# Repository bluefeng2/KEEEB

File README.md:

# KEEEB
Making a mechanical keyboard with LED lighting.
This keyboard has a 67 key layout, similar to a 60% keyboard.

I made this project, because I wanted a mechanical keyboard, and to learn how to design pcbs. I felt this would be a challenging project that would make me something I want to use daily.

.png)

## 3d Model:
Made in Fusion 360

.webp)

## PCB:
Made in KiCAD

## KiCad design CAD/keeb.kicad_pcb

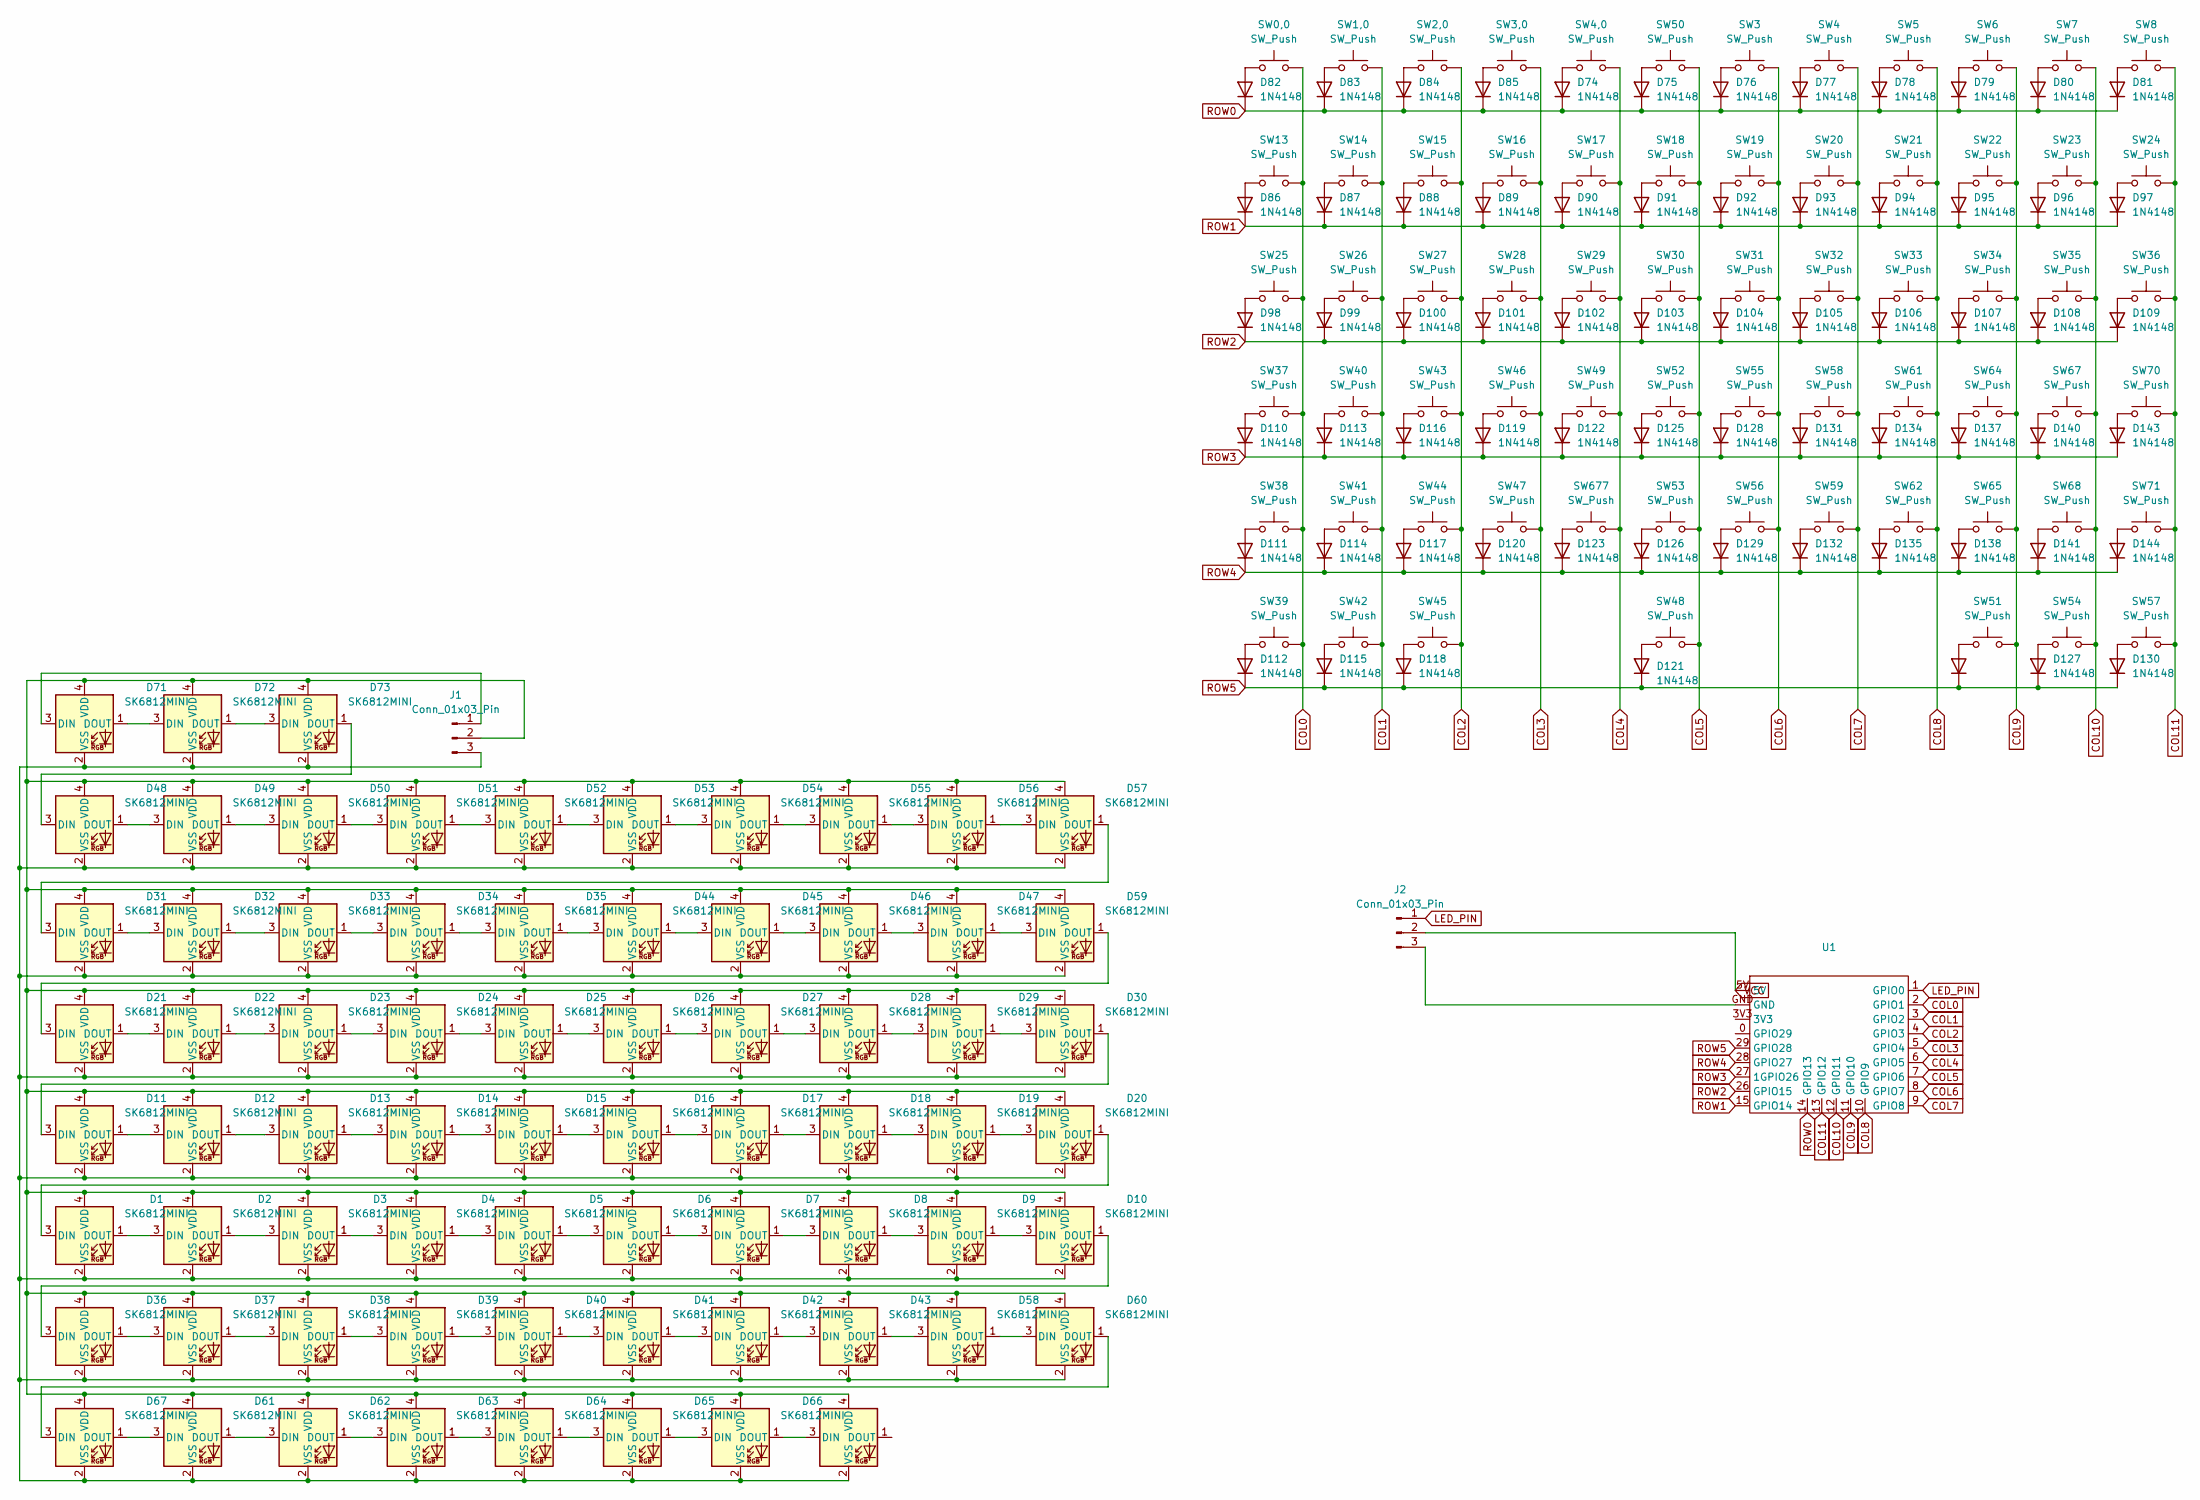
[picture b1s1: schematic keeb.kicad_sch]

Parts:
D1, D2, D3, D4, D5, D6, D7, D8, D9, D10, D11, D12, D13, D14, D15, D16, D17, D18, D19, D20, D21, D22, D23, D24, D25, D26, D27, D28, D29, D30, D31, D32, D33, D34, D35, D36, D37, D38, D39, D40, D41, D42, D43, D44, D45, D46, D47, D48, D49, D50, D51, D52, D53, D54, D55, D56, D57, D58, D59, D60, D61, D62, D63, D64, D65, D66, D67, D68, D71, D72, D73: SK6812MINI; LED_SK6812MINI_PLCC4_3.5x3.5mm_P1.75mm
D74, D75, D76, D77, D78, D79, D80, D81, D82, D83, D84, D85, D86, D87, D88, D89, D90, D91, D92, D93, D94, D95, D96, D97, D98, D99, D100, D101, D102, D103, D104, D105, D106, D107, D108, D109, D110, D111, D112, D113, D114, D115, D116, D117, D118, D119, D120, D121, D122, D123, D124, D125, D126, D127, D128, D129, D130, D131, D132, D134, D135, D137, D138, D140, D141, D143, D144: 1N4148; D_DO-35_SOD27_P7.62mm_Horizontal
J1, J2: Conn_01x03_Pin; PinHeader_1x03_P1.00mm_Vertical
SW0,0, SW1,0, SW2,0, SW3, SW3,0, SW4, SW4,0, SW5, SW6, SW8, SW14, SW17, SW18, SW20, SW21, SW22, SW23, SW24, SW27, SW28, SW29, SW30: SW_Push; SW_Cherry_MX_1.00u_Plate
SW7, SW15, SW16, SW19, SW26, SW31, SW32, SW33, SW34, SW35, SW36, SW38, SW40, SW41, SW43, SW44, SW46, SW47, SW49, SW50, SW52, SW55, SW57, SW58, SW59, SW61, SW64, SW65, SW67, SW68, SW71, SW677: SW_Push; SW_Cherry_MX_1.00u_PCB
SW13, SW39, SW53, SW54: SW_Push; SW_Cherry_MX_1.50u_PCB
SW25, SW70: SW_Push; SW_Cherry_MX_1.75u_PCB
SW37, SW62: SW_Push; SW_Cherry_MX_2.25u_PCB
SW42, SW45, SW51: SW_Push; SW_Cherry_MX_1.25u_PCB
SW48: SW_Push; SW_Cherry_MX_6.25u_PCB
SW56: SW_Push; SW_Cherry_MX_2.00u_PCB
U1: RP2040-Tiny

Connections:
COL0: SW0,0.2, SW13.2, SW25.2, SW37.2, SW38.2, SW39.2, U1.2 (GPIO1)
COL1: SW1,0.2, SW14.2, SW26.2, SW40.2, SW41.2, SW42.2, U1.3 (GPIO2)
COL2: SW2,0.2, SW15.2, SW27.2, SW43.2, SW44.2, SW45.2, U1.4 (GPIO3)
COL3: SW3,0.2, SW16.2, SW28.2, SW46.2, SW47.2, U1.5 (GPIO4)
COL4: SW4,0.2, SW17.2, SW29.2, SW49.2, SW677.2, U1.6 (GPIO5)
COL5: SW18.2, SW30.2, SW48.2, SW50.2, SW52.2, SW53.2, U1.7 (GPIO6)
COL6: SW3.2, SW19.2, SW31.2, SW55.2, SW56.2, U1.8 (GPIO7)
COL7: SW4.2, SW20.2, SW32.2, SW58.2, SW59.2, U1.9 (GPIO8)
COL8: SW5.2, SW21.2, SW33.2, SW61.2, SW62.2, U1.10 (GPIO9)
COL9: SW6.2, SW22.2, SW34.2, SW51.2, SW64.2, SW65.2, U1.11 (GPIO10)
COL10: SW7.2, SW23.2, SW35.2, SW54.2, SW67.2, SW68.2, U1.12 (GPIO11)
COL11: SW8.2, SW24.2, SW36.2, SW57.2, SW70.2, SW71.2, U1.13 (GPIO12)
LED_PIN: J2.1, U1.1 (GPIO0)
unnamed: D1.3 (DIN), D20.1 (DOUT)
unnamed: D1.1 (DOUT), D2.3 (DIN)
unnamed: D1.4 (VDD), D2.4 (VDD), D3.4 (VDD), D4.4 (VDD), D5.4 (VDD), D6.4 (VDD), D7.4 (VDD), D8.4 (VDD), D9.4 (VDD), D10.4 (VDD), D11.4 (VDD), D12.4 (VDD), D13.4 (VDD), D14.4 (VDD), D15.4 (VDD), D16.4 (VDD), D17.4 (VDD), D18.4 (VDD), D19.4 (VDD), D20.4 (VDD), D21.4 (VDD), D22.4 (VDD), D23.4 (VDD), D24.4 (VDD), D25.4 (VDD), D26.4 (VDD), D27.4 (VDD), D28.4 (VDD), D29.4 (VDD), D30.4 (VDD), D31.4 (VDD), D32.4 (VDD), D33.4 (VDD), D34.4 (VDD), D35.4 (VDD), D36.4 (VDD), D37.4 (VDD), D38.4 (VDD), D39.4 (VDD), D40.4 (VDD), D41.4 (VDD), D42.4 (VDD), D43.4 (VDD), D44.4 (VDD), D45.4 (VDD), D46.4 (VDD), D47.4 (VDD), D48.4 (VDD), D49.4 (VDD), D50.4 (VDD), D51.4 (VDD), D52.4 (VDD), D53.4 (VDD), D54.4 (VDD), D55.4 (VDD), D56.4 (VDD), D57.4 (VDD), D58.4 (VDD), D59.4 (VDD), D60.4 (VDD), D61.4 (VDD), D62.4 (VDD), D63.4 (VDD), D64.4 (VDD), D65.4 (VDD), D66.4 (VDD), D67.4 (VDD), D68.4 (VDD), D71.4 (VDD), D72.4 (VDD), D73.4 (VDD), J1.2
unnamed: D1.2 (VSS), D2.2 (VSS), D3.2 (VSS), D4.2 (VSS), D5.2 (VSS), D6.2 (VSS), D7.2 (VSS), D8.2 (VSS), D9.2 (VSS), D10.2 (VSS), D11.2 (VSS), D12.2 (VSS), D13.2 (VSS), D14.2 (VSS), D15.2 (VSS), D16.2 (VSS), D17.2 (VSS), D18.2 (VSS), D19.2 (VSS), D20.2 (VSS), D21.2 (VSS), D22.2 (VSS), D23.2 (VSS), D24.2 (VSS), D25.2 (VSS), D26.2 (VSS), D27.2 (VSS), D28.2 (VSS), D29.2 (VSS), D30.2 (VSS), D31.2 (VSS), D32.2 (VSS), D33.2 (VSS), D34.2 (VSS), D35.2 (VSS), D36.2 (VSS), D37.2 (VSS), D38.2 (VSS), D39.2 (VSS), D40.2 (VSS), D41.2 (VSS), D42.2 (VSS), D43.2 (VSS), D44.2 (VSS), D45.2 (VSS), D46.2 (VSS), D47.2 (VSS), D48.2 (VSS), D49.2 (VSS), D50.2 (VSS), D51.2 (VSS), D52.2 (VSS), D53.2 (VSS), D54.2 (VSS), D55.2 (VSS), D56.2 (VSS), D57.2 (VSS), D58.2 (VSS), D59.2 (VSS), D60.2 (VSS), D61.2 (VSS), D62.2 (VSS), D63.2 (VSS), D64.2 (VSS), D65.2 (VSS), D66.2 (VSS), D67.2 (VSS), D68.2 (VSS), D71.2 (VSS), D72.2 (VSS), D73.2 (VSS), J1.3
unnamed: D2.1 (DOUT), D3.3 (DIN)
unnamed: D3.1 (DOUT), D4.3 (DIN)
unnamed: D4.1 (DOUT), D5.3 (DIN)
unnamed: D5.1 (DOUT), D6.3 (DIN)
unnamed: D6.1 (DOUT), D7.3 (DIN)
unnamed: D7.1 (DOUT), D8.3 (DIN)
unnamed: D8.1 (DOUT), D9.3 (DIN)
unnamed: D9.1 (DOUT), D10.3 (DIN)
unnamed: D10.1 (DOUT), D36.3 (DIN)
unnamed: D11.3 (DIN), D30.1 (DOUT)
unnamed: D11.1 (DOUT), D12.3 (DIN)
unnamed: D12.1 (DOUT), D13.3 (DIN)
unnamed: D13.1 (DOUT), D14.3 (DIN)
unnamed: D14.1 (DOUT), D15.3 (DIN)
unnamed: D15.1 (DOUT), D16.3 (DIN)
unnamed: D16.1 (DOUT), D17.3 (DIN)
unnamed: D17.1 (DOUT), D18.3 (DIN)
unnamed: D18.1 (DOUT), D19.3 (DIN)
unnamed: D19.1 (DOUT), D20.3 (DIN)
unnamed: D21.3 (DIN), D59.1 (DOUT)
unnamed: D21.1 (DOUT), D22.3 (DIN)
unnamed: D22.1 (DOUT), D23.3 (DIN)
unnamed: D23.1 (DOUT), D24.3 (DIN)
unnamed: D24.1 (DOUT), D25.3 (DIN)
unnamed: D25.1 (DOUT), D26.3 (DIN)
unnamed: D26.1 (DOUT), D27.3 (DIN)
unnamed: D27.1 (DOUT), D28.3 (DIN)
unnamed: D28.1 (DOUT), D29.3 (DIN)
unnamed: D29.1 (DOUT), D30.3 (DIN)
unnamed: D31.3 (DIN), D57.1 (DOUT)
unnamed: D31.1 (DOUT), D32.3 (DIN)
unnamed: D32.1 (DOUT), D33.3 (DIN)
unnamed: D33.1 (DOUT), D34.3 (DIN)
unnamed: D34.1 (DOUT), D35.3 (DIN)
unnamed: D35.1 (DOUT), D44.3 (DIN)
unnamed: D36.1 (DOUT), D37.3 (DIN)
unnamed: D37.1 (DOUT), D38.3 (DIN)
unnamed: D38.1 (DOUT), D39.3 (DIN)
unnamed: D39.1 (DOUT), D40.3 (DIN)
unnamed: D40.1 (DOUT), D41.3 (DIN)
unnamed: D41.1 (DOUT), D42.3 (DIN)
unnamed: D42.1 (DOUT), D43.3 (DIN)
unnamed: D43.1 (DOUT), D58.3 (DIN)
unnamed: D44.1 (DOUT), D45.3 (DIN)
unnamed: D45.1 (DOUT), D46.3 (DIN)
unnamed: D46.1 (DOUT), D47.3 (DIN)
unnamed: D47.1 (DOUT), D59.3 (DIN)
unnamed: D48.3 (DIN), D73.1 (DOUT)
unnamed: D48.1 (DOUT), D49.3 (DIN)
unnamed: D49.1 (DOUT), D50.3 (DIN)
unnamed: D50.1 (DOUT), D51.3 (DIN)
unnamed: D51.1 (DOUT), D52.3 (DIN)
unnamed: D52.1 (DOUT), D53.3 (DIN)
unnamed: D53.1 (DOUT), D54.3 (DIN)
unnamed: D54.1 (DOUT), D55.3 (DIN)
unnamed: D55.1 (DOUT), D56.3 (DIN)
unnamed: D56.1 (DOUT), D57.3 (DIN)
unnamed: D58.1 (DOUT), D60.3 (DIN)
unnamed: D60.1 (DOUT), D67.3 (DIN)
unnamed: D61.3 (DIN), D67.1 (DOUT)
unnamed: D61.1 (DOUT), D62.3 (DIN)
unnamed: D62.1 (DOUT), D63.3 (DIN)
unnamed: D63.1 (DOUT), D64.3 (DIN)
unnamed: D64.1 (DOUT), D65.3 (DIN)
unnamed: D65.1 (DOUT), D66.3 (DIN)
unnamed: D66.1 (DOUT), D68.3 (DIN)
unnamed: D71.3 (DIN), J1.1
unnamed: D71.1 (DOUT), D72.3 (DIN)
unnamed: D72.1 (DOUT), D73.3 (DIN)
unnamed: D74.2 (A), SW4,0.1
unnamed: D75.2 (A), SW50.1
unnamed: D76.2 (A), SW3.1
unnamed: D77.2 (A), SW4.1
unnamed: D78.2 (A), SW5.1
unnamed: D79.2 (A), SW6.1
unnamed: D80.2 (A), SW7.1
unnamed: D81.2 (A), SW8.1
unnamed: D82.2 (A), SW0,0.1
unnamed: D83.2 (A), SW1,0.1
unnamed: D84.2 (A), SW2,0.1
unnamed: D85.2 (A), SW3,0.1
unnamed: D86.2 (A), SW13.1
unnamed: D87.2 (A), SW14.1
unnamed: D88.2 (A), SW15.1
unnamed: D89.2 (A), SW16.1
unnamed: D90.2 (A), SW17.1
unnamed: D91.2 (A), SW18.1
unnamed: D92.2 (A), SW19.1
unnamed: D93.2 (A), SW20.1
unnamed: D94.2 (A), SW21.1
unnamed: D95.2 (A), SW22.1
unnamed: D96.2 (A), SW23.1
unnamed: D97.2 (A), SW24.1
unnamed: D98.2 (A), SW25.1
unnamed: D99.2 (A), SW26.1
unnamed: D100.2 (A), SW27.1
unnamed: D101.2 (A), SW28.1
unnamed: D102.2 (A), SW29.1
unnamed: D103.2 (A), SW30.1
unnamed: D104.2 (A), SW31.1
unnamed: D105.2 (A), SW32.1
unnamed: D106.2 (A), SW33.1
unnamed: D107.2 (A), SW34.1
unnamed: D108.2 (A), SW35.1
unnamed: D109.2 (A), SW36.1
unnamed: D110.2 (A), SW37.1
unnamed: D111.2 (A), SW38.1
unnamed: D112.2 (A), SW39.1
unnamed: D113.2 (A), SW40.1
unnamed: D114.2 (A), SW41.1
unnamed: D115.2 (A), SW42.1
unnamed: D116.2 (A), SW43.1
unnamed: D117.2 (A), SW44.1
unnamed: D118.2 (A), SW45.1
unnamed: D119.2 (A), SW46.1
unnamed: D120.2 (A), SW47.1
unnamed: D121.2 (A), SW48.1
unnamed: D122.2 (A), SW49.1
unnamed: D123.2 (A), SW677.1
unnamed: D124.2 (A), SW51.1
unnamed: D125.2 (A), SW52.1
unnamed: D126.2 (A), SW53.1
unnamed: D127.2 (A), SW54.1
unnamed: D128.2 (A), SW55.1
unnamed: D129.2 (A), SW56.1
unnamed: D130.2 (A), SW57.1
unnamed: D131.2 (A), SW58.1
unnamed: D132.2 (A), SW59.1
unnamed: D134.2 (A), SW61.1
unnamed: D135.2 (A), SW62.1
unnamed: D137.2 (A), SW64.1
unnamed: D138.2 (A), SW65.1
unnamed: D140.2 (A), SW67.1
unnamed: D141.2 (A), SW68.1
unnamed: D143.2 (A), SW70.1
unnamed: D144.2 (A), SW71.1
unnamed: J2.3, U1.GND
ROW0: D74.1 (K), D75.1 (K), D76.1 (K), D77.1 (K), D78.1 (K), D79.1 (K), D80.1 (K), D81.1 (K), D82.1 (K), D83.1 (K), D84.1 (K), D85.1 (K), U1.14 (GPIO13)
ROW1: D86.1 (K), D87.1 (K), D88.1 (K), D89.1 (K), D90.1 (K), D91.1 (K), D92.1 (K), D93.1 (K), D94.1 (K), D95.1 (K), D96.1 (K), D97.1 (K), U1.15 (GPIO14)
ROW2: D98.1 (K), D99.1 (K), D100.1 (K), D101.1 (K), D102.1 (K), D103.1 (K), D104.1 (K), D105.1 (K), D106.1 (K), D107.1 (K), D108.1 (K), D109.1 (K), U1.26 (GPIO15)
ROW3: D110.1 (K), D113.1 (K), D116.1 (K), D119.1 (K), D122.1 (K), D125.1 (K), D128.1 (K), D131.1 (K), D134.1 (K), D137.1 (K), D140.1 (K), D143.1 (K), U1.27 (1GPIO26)
ROW4: D111.1 (K), D114.1 (K), D117.1 (K), D120.1 (K), D123.1 (K), D126.1 (K), D129.1 (K), D132.1 (K), D135.1 (K), D138.1 (K), D141.1 (K), D144.1 (K), U1.28 (GPIO27)
ROW5: D112.1 (K), D115.1 (K), D118.1 (K), D121.1 (K), D124.1 (K), D127.1 (K), D130.1 (K), U1.29 (GPIO28)
VCC: J2.2, U1.5V

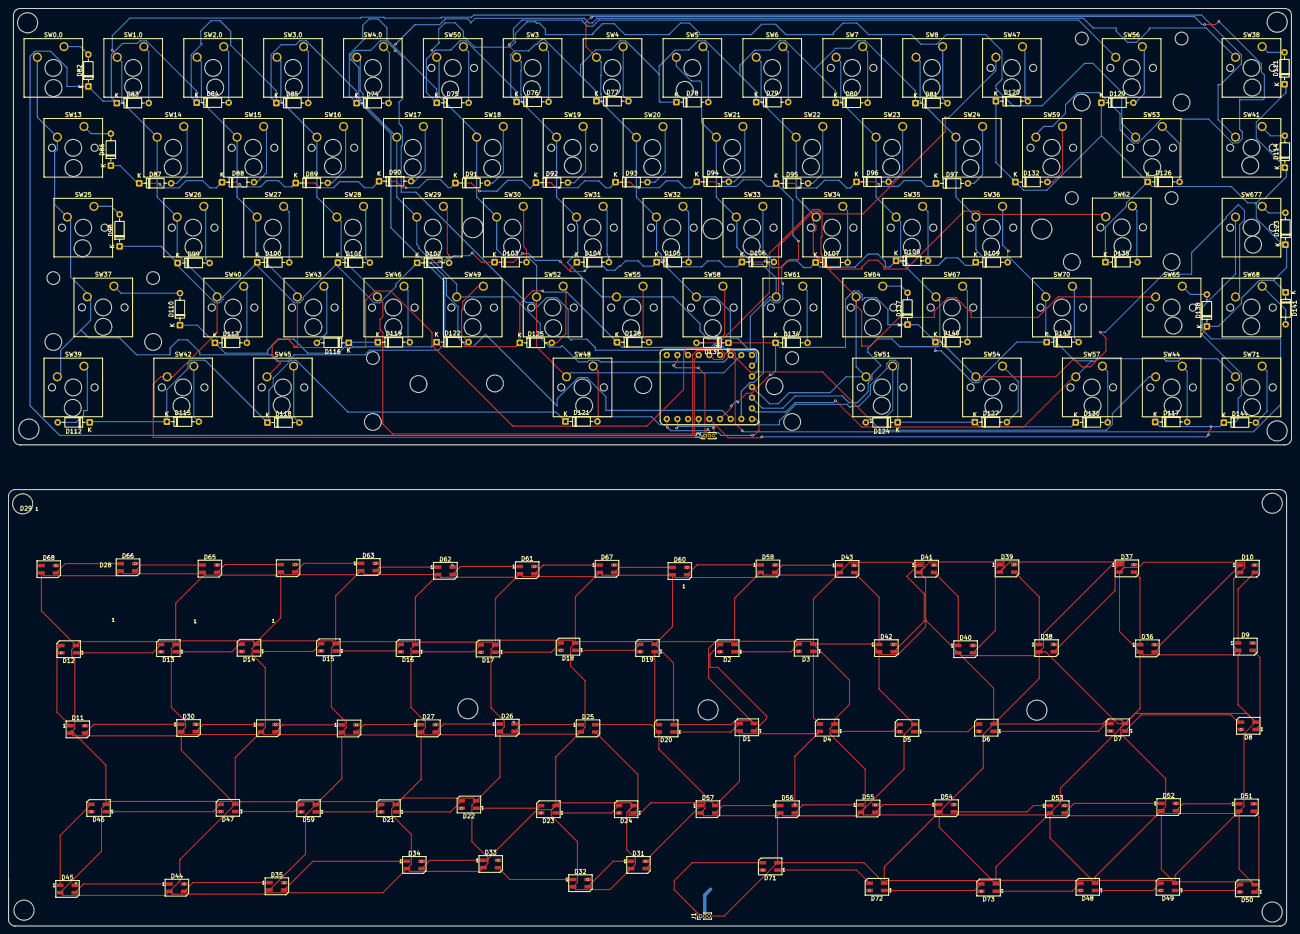
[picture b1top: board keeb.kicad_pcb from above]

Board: 2 copper layers, 306.0 x 218.8 mm, 208 parts (0 on the bottom side), 161 nets.

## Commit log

2025-12-01 added files
